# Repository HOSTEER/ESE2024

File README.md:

# ESE2024
    Emilie Butruille
    Louis Liénart
    Théo Césari
    Victor Lesne
------

Activer doxygen dans les propriétés du projet -> général C/C++, tuto doxygen https://www.youtube.com/watch?v=GC9Xy7nLxyw

Pour importer un projet sur cubeIDE, il faut faire "File" -> "Import" -> "General" -> "Project from Folder or Archive" puis sélectionner le directory (exemple "C:\Users\louis\Desktop\ProjetCubeIDE") et ensuite faire "finish".
Après ça, il faut régénérer des fichiers du code, donc cliquer sur "Device configuration tool Code generation"

Avec GitBash, pour retirer un fichier "add" par erreur faire un "git reset nom_du_fichier", un reset seul retirera tout les add fait.

Convention à avoir pour le stockage des sources :
pour stocker les lib créer faire un dossier source "Prod" avec comme sous-fichier "Inc" et "Src"
Ensuite les ajouter dans "Project" -> "Properties" -> "C/C++ General" -> "Paths and Symbols" -> "add" -> entrer "Prod/Inc" et faire ok.

Pour vérifier qu'une branch est ok, cloner un 2nd repo de la branch et la tester pour vérifier l'absence d'erreurs, sinon ça veut dire qu'il manque un truc au commit.

Ensuite il faut résoudre les conflits entre .cproject ( globalement garder le code du main ); .ioc (globalement fusionner les pins ajoutés et faire gaffe au pin, en double) et enfin le main.c ( où il faut fusionner )

conso moyenne 300 mA

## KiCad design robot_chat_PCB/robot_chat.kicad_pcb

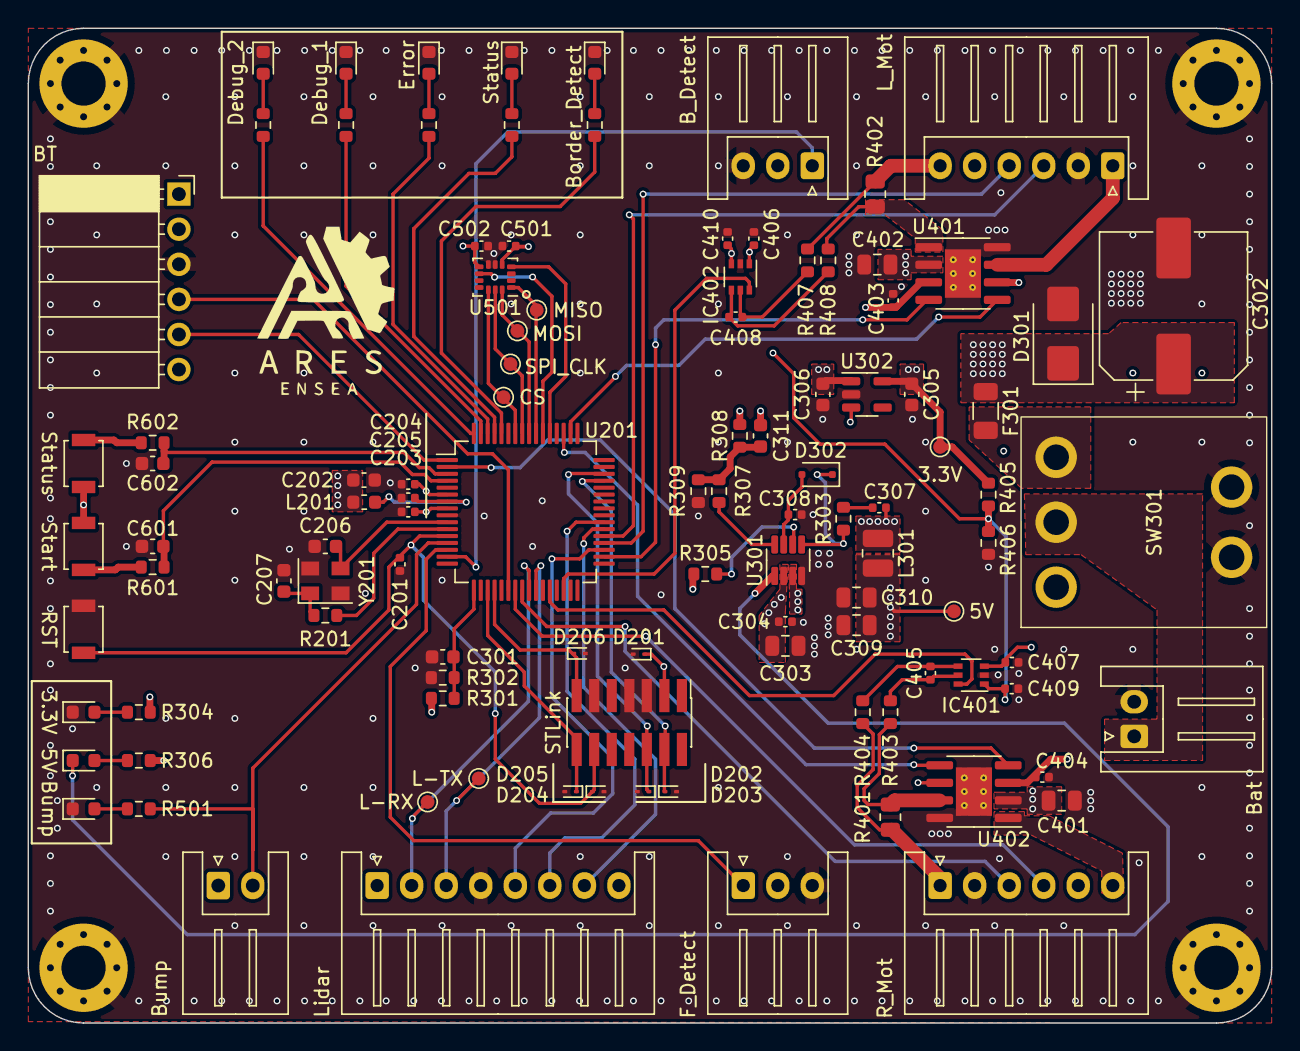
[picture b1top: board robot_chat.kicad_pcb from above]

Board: 4 copper layers, 90.0 x 72.0 mm, 111 parts (0 on the bottom side), 78 nets.

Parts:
+3V301: 3.3V; TestPoint_Pad_D1.0mm
+5V301: 5V; TestPoint_Pad_D1.0mm
C201, C203, C204, C205, C403, C404, C405, C406, C407, C408, C409, C410: 0.1uF; C_0402_1005Metric
C202: 4.7uF; C_0603_1608Metric
C206, C207: 10p; C_0603_1608Metric
C301, C305, C306, C601, C602: 1uF; C_0603_1608Metric
C302: 470uF; CP_Elec_10x10.5
C303, C309, C310, C401, C402: 22uF; C_0805_2012Metric
C304, C307, C308: 0,1uF; C_0402_1005Metric
C311: 15pF; C_0603_1608Metric
C501, C502: 0.1u; C_0402_1005Metric
CS201: CS; TestPoint_Pad_D1.0mm
D201, D202, D203, D204, D205, D206: D_SOD-923
D301: D_SMB
D302: 1N4148; D_SOD-323F
D303: 3.3V; LED_0603_1608Metric
D304: 5V; LED_0603_1608Metric
D501: Bump; LED_0603_1608Metric
D601: Border_Detect; LED_0603_1608Metric
D602: Status; LED_0603_1608Metric
D603: Error; LED_0603_1608Metric
D604: Debug_1; LED_0603_1608Metric
D605: Debug_2; LED_0603_1608Metric
F301: 10A; Fuse_1206_3216Metric
H101, H102, H103, H104: MountingHole_Pad; MountingHole_3.2mm_M3_Pad_Via
IC401, IC402: NCS199A3RSQT2G; SOT-363_SC-70-6
J201: STLink; PinHeader_2x07_P1.27mm_Vertical_SMD
J301: Bat; JST_XH_S2B-XH-A_1x02_P2.50mm_Horizontal
J401: L_Mot; JST_XH_S6B-XH-A_1x06_P2.50mm_Horizontal
J402: R_Mot; JST_XH_S6B-XH-A_1x06_P2.50mm_Horizontal
J501: Bump; JST_XH_S2B-XH-A_1x02_P2.50mm_Horizontal
J502: Lidar; JST_XH_S8B-XH-A_1x08_P2.50mm_Horizontal
J503: B_Detect; JST_XH_S3B-XH-A_1x03_P2.50mm_Horizontal
J504: F_Detect; JST_XH_S3B-XH-A_1x03_P2.50mm_Horizontal
J601: BT; PinSocket_1x06_P2.54mm_Horizontal
L201: 2.2u; L_0603_1608Metric
L301: 4.7uH; L_1008_2520Metric
LIDAR_RX201: L-RX; TestPoint_Pad_D1.0mm
LIDAR_TX201: L-TX; TestPoint_Pad_D1.0mm
R201, R403, R404, R407, R408: 10R; R_0603_1608Metric
R301: 22k; R_0603_1608Metric
R302: 10k; R_0603_1608Metric
R303: 20; R_0603_1608Metric
R304, R306, R501, R601, R602, R603, R604, R605, R606, R607: 1k; R_0603_1608Metric
R305, R405, R406: 100k; R_0603_1608Metric
R307: 16k; R_0603_1608Metric
R308: 40.2k; R_0603_1608Metric
R309: 7.68k; R_0603_1608Metric
R401, R402: 0.015; R_0805_2012Metric
SDI201: MOSI; TestPoint_Pad_D1.0mm
SDO201: MISO; TestPoint_Pad_D1.0mm
SPI_CLK201: SPI_CLK; TestPoint_Pad_D1.0mm
SW201: RST; SW_SPST_B3U-1000P
SW301: SW_SPDT_MSM; Toggle_Switch
SW601: Start; SW_SPST_B3U-1000P
SW602: Status; SW_SPST_B3U-1000P
U201: STM32G070RBTx; LQFP-64_10x10mm_P0.5mm
U301: MP1475DJ-LF-P; TSOT-23-8
U302: MIC5317-3.3xM5; SOT-23-5
U401, U402: ZXBM5210-SP; SOIC-8-1EP_3.9x4.9mm_P1.27mm_EP2.62x3.51mm_ThermalVias
U501: LSM6DSM; LGA-14_3x2.5mm_P0.5mm_LayoutBorder3x4y
Y201: 16MHz; Crystal_SMD_EuroQuartz_MT-4Pin_3.2x2.5mm

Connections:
+3.3V: +3V301.1, C202.1, C203.1, C204.1, C305.1, C403.1, C404.1, C407.1, C410.1, C501.1, C502.1, D201.1 (A1), IC401.3 (VS), IC402.3 (VS), J201.3, J401.5, J402.5, J501.1, J503.2, J504.2, L201.1, R304.2, R405.1, SW601.2, SW602.2, U201.6 (VBAT), U201.8 (VDD), U302.5 (VOUT), U401.3 (VDD), U401.6 (VREF), U402.3 (VDD), U402.6 (VREF), U501.5 (VDDIO), U501.8 (VDD)
+5V: +5V301.1, C306.1, C309.1, C310.1, C311.2, J502.1, J601.2, L301.2, R306.1, R308.2, U302.1 (VIN), U302.3 (EN)
+7.5V: C302.1, C303.1, C304.1, C401.1, C402.1, D301.1 (A1), F301.1, R301.1, R305.1, U301.2 (IN), U401.2 (VM), U402.2 (VM)
/HMI/BT_RX: J601.5, U201.1 (PC11)
/HMI/BT_TX: J601.4, U201.22 (PA5)
/HMI/PB_GAME_START: C601.1, R601.1, U201.4 (PC14)
/HMI/PB_GAME_STATUS: C602.1, R602.1, U201.3 (PC13)
/Motor drivers/ENCODER_L_A: J401.3, U201.37 (PA9/NC)
/Motor drivers/ENCODER_L_B: J401.4, U201.36 (PA8)
/Motor drivers/ENCODER_R_A: J402.3, U201.24 (PA7)
/Motor drivers/ENCODER_R_B: J402.4, U201.23 (PA6)
/Motor drivers/FWD_L: U201.34 (PB14), U401.4 (FWD)
/Motor drivers/FWD_R: U201.2 (PC12), U402.4 (FWD)
/Motor drivers/IN_L+: C408.2, IC402.4 (IN+), R408.2
/Motor drivers/IN_L-: C408.1, IC402.5 (IN-), R407.2
/Motor drivers/IN_R+: C405.2, IC401.4 (IN+), R404.2
/Motor drivers/IN_R-: C405.1, IC401.5 (IN-), R403.2
/Motor drivers/I_READ_L: IC402.6 (OUT), U201.30 (PB10)
/Motor drivers/I_READ_R: IC401.6 (OUT), U201.28 (PB1)
/Motor drivers/MOTOR_L+: J401.1, U401.7 (OUT2)
/Motor drivers/MOTOR_L-: R402.2, R408.1, U401.1 (OUT1)
/Motor drivers/MOTOR_R+: R401.2, R403.1, U402.7 (OUT2)
/Motor drivers/MOTOR_R-: J402.6, U402.1 (OUT1)
/Motor drivers/REV_L: U201.50 (PD0), U401.5 (REV)
/Motor drivers/REV_R: U201.51 (PD1), U402.5 (REV)
/Motor drivers/RSENSE_L-: J401.6, R402.1, R407.1
/Motor drivers/RSENSE_R-: J402.1, R401.1, R404.1
/Motor drivers/VREF: C406.1, C409.1, IC401.1 (REF), IC402.1 (REF), R405.2, R406.1
/Power Supply/BST: D302.1 (K), R303.1, U301.5 (BST)
/Power Supply/EN/SYNC: R305.2, U301.6 (EN/SYNC)
/Power Supply/FB: R307.1, U301.8 (FB)
/Power Supply/PG: D304.1 (K), U301.1 (PG)
/Power Supply/SW: C307.2, L301.1, U301.3 (SW)
/Power Supply/VBAT_READ: C301.2, R301.2, R302.1, U201.17 (PA0)
/Power Supply/VCC: C308.1, D302.2 (A), U301.7 (VCC)
/STM/BACK_BORDER_DETECT: J503.1, U201.15 (PC2)
/STM/BUMPER_SW: J501.2, R501.2, U201.13 (PC0)
/STM/FRONT_BORDER_DETECT: J504.1, U201.14 (PC1)
/STM/IMU_INT1: U201.53 (PD3), U501.4 (INT1)
/STM/IMU_INT2: U201.54 (PD4), U501.9 (INT2)
/STM/IMU_SPI_CLK: SPI_CLK201.1, U201.57 (PB3), U501.13 (SCL)
/STM/IMU_SPI_CS: CS201.1, U201.58 (PB4), U501.12 (CS)
/STM/IMU_SPI_SDI: SDI201.1, U201.56 (PD6), U501.14 (SDA)
/STM/IMU_SPI_SDO: SDO201.1, U201.55 (PD5), U501.1 (SDO/SA0)
/STM/LIDAR_EN: J502.7, U201.38 (PC6)
/STM/LIDAR_RANGING_EN: J502.6, U201.39 (PC7)
/STM/LIDAR_RX: J502.2, LIDAR_RX201.1, U201.25 (PC4)
/STM/LIDAR_SPEED: J502.5, U201.35 (PB15)
/STM/LIDAR_TX: J502.3, LIDAR_TX201.1, U201.26 (PC5)
/STM/QUARTZ_0: C206.2, U201.10 (PF0), Y201.3
/STM/QUARTZ_1: R201.2, U201.11 (PF1)
/STM/STLINK_RX: D206.1 (A1), J201.13, U201.20 (PA3)
/STM/STLINK_TX: D205.1 (A1), J201.14, U201.19 (PA2)
/STM/SWCLK: D203.1 (A1), J201.6, U201.46 (PA14)
/STM/SWDIO: D202.1 (A1), J201.4, U201.45 (PA13)
/STM/VREF+: C205.2, L201.2, U201.7 (VREF+)
/STM/~RST: C201.2, D204.1 (A1), J201.12, SW201.2, U201.12 (NRST)
GND: C201.1, C202.2, C203.2, C204.2, C205.1, C206.1, C207.1, C301.1, C302.2, C303.2, C304.2, C305.2, C306.2, C308.2, C309.2, C310.2, C401.2, C402.2, C403.2, C404.2, C406.2, C407.2, C409.2, C410.2, C501.2, C502.2, C601.2, C602.2, D201.2 (A2), D202.2 (A2), D203.2 (A2), D204.2 (A2), D205.2 (A2), D206.2 (A2), D301.2 (A2), D303.1 (K), D501.1 (K), D601.1 (K), D602.1 (K), D603.1 (K), D604.1 (K), D605.1 (K), H101.1, H102.1, H103.1, H104.1, IC401.2 (GND), IC402.2 (GND), J201.5, J201.7, J201.11, J301.2, J401.2, J402.2, J502.4, J503.3, J504.3, J601.3, R302.2, R309.2, R406.2, SW201.1, SW301.4, SW301.5, U201.9 (VSS), U301.4 (GND), U302.2 (GND), U401.8 (GND), U401.9 (GND), U402.8 (GND), U402.9 (GND), U501.6 (GND), U501.7 (GND), Y201.2, Y201.4
unnamed: C207.2, R201.1, Y201.1
unnamed: C307.1, R303.2
unnamed: C311.1, R307.2, R308.1, R309.1
unnamed: D303.2 (A), R304.1
unnamed: D304.2 (A), R306.2
unnamed: D501.2 (A), R501.1
unnamed: D601.2 (A), R603.2
unnamed: D602.2 (A), R604.2
unnamed: D603.2 (A), R605.2
unnamed: D604.2 (A), R606.2
unnamed: D605.2 (A), R607.2
unnamed: F301.2, SW301.1
unnamed: J301.1, SW301.2
unnamed: R601.2, SW601.1
unnamed: R602.2, SW602.1
USER_LED_0: R603.1, U201.60 (PB6)
USER_LED_1: R604.1, U201.61 (PB7)
USER_LED_2: R605.1, U201.62 (PB8)
USER_LED_3: R606.1, U201.63 (PB9)
USER_LED_4: R607.1, U201.64 (PC10)

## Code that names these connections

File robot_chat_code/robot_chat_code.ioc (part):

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Mcu.Name=STM32G070RBTx
Mcu.Package=LQFP64
Mcu.UserName=STM32G070RBTx
PA0.GPIOParameters=GPIO_Label
PA0.GPIO_Label=BAT_ADC
PA0.Mode=IN0
PA0.Signal=ADC1_IN0
PA13.Mode=Serial_Wire
PA13.Signal=SYS_SWDIO
PA14-BOOT0.Mode=Serial_Wire
PA14-BOOT0.Signal=SYS_SWCLK
PA2.GPIOParameters=GPIO_Label
PA2.GPIO_Label=ST_LINK_TX
PA2.Mode=Asynchronous
PA2.Signal=USART2_TX
PA3.GPIOParameters=GPIO_Label
PA3.GPIO_Label=ST_LINK_RX
PA3.Mode=Asynchronous
PA3.Signal=USART2_RX
PA5.GPIOParameters=GPIO_Label
PA5.GPIO_Label=BT_TX
PA5.Mode=Asynchronous
PA5.Signal=USART3_TX
PA6.GPIOParameters=GPIO_Label
PA6.GPIO_Label=R_ENCODE_B
PA6.Signal=S_TIM3_CH1
PA7.GPIOParameters=GPIO_Label
PA7.GPIO_Label=R_ENCODE_A
PA7.Signal=S_TIM3_CH2
PA8.GPIOParameters=GPIO_Label
PA8.GPIO_Label=L_ENCODE_B
PA8.Signal=S_TIM1_CH1
PA9.GPIOParameters=GPIO_Label
PA9.GPIO_Label=L_ENCODE_A
PA9.Signal=S_TIM1_CH2
PB1.GPIOParameters=GPIO_Label
PB1.GPIO_Label=I_READ_R
PB1.Mode=IN9
PB1.Signal=ADC1_IN9
PB10.GPIOParameters=GPIO_Label
PB10.GPIO_Label=I_READ_L
PB10.Mode=IN11
PB10.Signal=ADC1_IN11
PB14.GPIOParameters=GPIO_Label
PB14.GPIO_Label=L_FORWARD
PB14.Signal=S_TIM15_CH1
PB15.GPIOParameters=GPIO_Label
PB15.GPIO_Label=LIDAR_SPEED
PB15.Signal=S_TIM15_CH2
PB3.GPIOParameters=GPIO_Label
PB3.GPIO_Label=IMU_SPI_CLK
PB3.Mode=Full_Duplex_Master
PB3.Signal=SPI1_SCK
PB4.GPIOParameters=PinState,GPIO_Label
PB4.GPIO_Label=IMU_SPI_CS
PB4.PinState=GPIO_PIN_SET
PB4.Signal=GPIO_Output
PB6.GPIOParameters=GPIO_Label
PB6.GPIO_Label=USER_LED0
PB6.Signal=GPIO_Output
PB7.GPIOParameters=GPIO_Label
PB7.GPIO_Label=USER_LED1
PB7.Signal=GPIO_Output
PB8.GPIOParameters=GPIO_Label
PB8.GPIO_Label=USER_LED2
PB8.Signal=GPIO_Output
PB9.GPIOParameters=GPIO_Label
PB9.GPIO_Label=USER_LED3
PB9.Signal=GPIO_Output
PC0.GPIOParameters=GPIO_Label
PC0.GPIO_Label=BUMP_EXTI
PC0.Signal=GPIO_Input
PC1.GPIOParameters=GPIO_PuPd,GPIO_Label,GPIO_ModeDefaultEXTI
PC1.GPIO_Label=FBD_EXTI1
PC1.GPIO_ModeDefaultEXTI=GPIO_MODE_IT_RISING_FALLING
PC1.GPIO_PuPd=GPIO_PULLDOWN
PC1.Signal=GPXTI1
PC10.GPIOParameters=GPIO_Label
PC10.GPIO_Label=USER_LED4
PC10.Signal=GPIO_Output
PC11.GPIOParameters=GPIO_Label
PC11.GPIO_Label=BT_RX
PC11.Mode=Asynchronous
PC11.Signal=USART3_RX
PC12.GPIOParameters=GPIO_Label
PC12.GPIO_Label=R_FORWARD
PC12.Signal=S_TIM14_CH1
PC13.GPIOParameters=GPIO_PuPd,GPIO_Label,GPIO_ModeDefaultEXTI
PC13.GPIO_Label=BTN_GAME_STATUS
PC13.GPIO_ModeDefaultEXTI=GPIO_MODE_IT_RISING
PC13.GPIO_PuPd=GPIO_PULLDOWN
PC13.Signal=GPXTI13
PC14-OSC32_IN\ (PC14).GPIOParameters=GPIO_PuPd,GPIO_Label
PC14-OSC32_IN\ (PC14).GPIO_Label=BTN_GAME_START
PC14-OSC32_IN\ (PC14).GPIO_PuPd=GPIO_PULLDOWN
PC14-OSC32_IN\ (PC14).Signal=GPXTI14
PC2.GPIOParameters=GPIO_PuPd,GPIO_Label,GPIO_ModeDefaultEXTI
PC2.GPIO_Label=BBD_EXTI2
PC2.GPIO_ModeDefaultEXTI=GPIO_MODE_IT_RISING_FALLING
PC2.GPIO_PuPd=GPIO_PULLDOWN
PC2.Signal=GPXTI2
PC4.GPIOParameters=GPIO_Label
PC4.GPIO_Label=LIDAR_TX
PC4.Mode=Asynchronous
PC4.Signal=USART1_TX
PC5.GPIOParameters=GPIO_Label
PC5.GPIO_Label=LIDAR_RX
PC5.Mode=Asynchronous
PC5.Signal=USART1_RX
PC6.GPIOParameters=GPIO_Label
PC6.GPIO_Label=LIDAR_EN
PC6.Signal=GPIO_Output
PC7.GPIOParameters=GPIO_Label
PC7.GPIO_Label=LIDAR_RANGING_EN
PC7.Signal=GPIO_Output
PD0.GPIOParameters=GPIO_Label
PD0.GPIO_Label=L_REVERSE
PD0.Signal=S_TIM16_CH1
PD1.GPIOParameters=GPIO_Label
PD1.GPIO_Label=R_REVERSE
PD1.Signal=S_TIM17_CH1
PD3.GPIOParameters=GPIO_Label
PD3.GPIO_Label=IMU_INT1
PD3.Signal=GPXTI3
PD4.GPIOParameters=GPIO_Label
PD4.GPIO_Label=IMU_INT2
PD4.Signal=GPXTI4
PD5.GPIOParameters=GPIO_Label
PD5.GPIO_Label=IMU_SPI_SDO
PD5.Mode=Full_Duplex_Master
PD5.Signal=SPI1_MISO
PD6.GPIOParameters=GPIO_Label
PD6.GPIO_Label=IMU_SPI_SDI
PD6.Mode=Full_Duplex_Master
PD6.Signal=SPI1_MOSI
PF0-OSC_IN\ (PF0).Mode=HSE-External-Oscillator
PF0-OSC_IN\ (PF0).Signal=RCC_OSC_IN
PF1-OSC_OUT\ (PF1).Mode=HSE-External-Oscillator
PF1-OSC_OUT\ (PF1).Signal=RCC_OSC_OUT
RCC.HSE_VALUE=16000000
RCC.SYSCLKFreq_VALUE=64000000
RCC.SYSCLKSource=RCC_SYSCLKSOURCE_PLLCLK
board=custom

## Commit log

2023-09-18 schema fonctionnement
2023-09-18 BOM v1
2023-09-18 test
2023-09-18 ready2
2023-09-18 ready5
2023-09-18 ready10
2023-09-19 Schema fonctionnel v1
2023-09-19 Schema fonctionnel v2
2023-09-19 image readme
2023-09-19 image readme v2
2023-09-19 AddingPins
2023-09-19 image readme v3
2023-09-19 image readme v4 et datasheets
2023-09-19 shah
2023-09-19 PIN CubeIDE et PCB
2023-09-19 Project re-upload
2023-09-20 ajout BOM v2
2023-09-20 premier modif
2023-09-20 pcb alim et connecteurs
2023-09-21 addPin
2023-09-21 Ajout lecture courant et enable lidar sur ioc
2023-09-21 Modif PCB
2023-09-21 lidar_dev
2023-09-22 Ajout IMU
2023-09-22 Ajout IMU pcb
2023-09-25 addingLibLIdar
2023-09-25 Labels non reliés pour BOM
2023-09-25 PCB revu
2023-09-25 Ajout game start
2023-09-25 ajout BOM
2023-09-25 progessLib
2023-09-25 PCB final avec BOM
2023-09-27 lib change
2023-09-28 upgrade_lib_fonctionnel
2023-09-28 Placement composants
2023-09-28 upgrade_lecture_first_frame
2023-09-29 minimodif
2023-10-02 Mise à jour placement
2023-10-02 changed Rsense position
2023-10-02 lecture_angle
2023-10-03 parser_ok
2023-10-03 Mise à jour led bumper
2023-10-04 function_simplification
2023-10-04 gettingsmpl
2023-10-05 Lidar data extracted
2023-10-05 Routage
2023-10-06 Lidar data computing
2023-10-06 improve lib
2023-10-09 Nom des fonctions & variables changé de ylidar à ydlidar
2023-10-09 Routage final v1
2023-10-09 changed pinout
2023-10-09 routage final v1.1
2023-10-09 correct lidar lib and adding lidar visualizer
2023-10-16 Routage final v1.2
2023-10-16 adding encoder test project
2023-10-26 fixed DRC, added html bom
2023-11-01 nom plus simple dans le main de variable de structure et re-ajout des distances sur 360 deg avec un choix ifdef
2023-11-01 simplifying variable name in function by lidar instead of ydlidar_x4
2023-11-13 test MCU avec freetos et test user led ok
2023-11-13 ajout du BT pour le print
2023-11-13 Start of IMU driver
2023-11-13 IMU dev init
2023-11-13 ajout lidar en cours, ajouter l'etape de calcule
2023-11-22 reception et envoie des donnees lidar utilisable
2023-11-23 SPI communicant
2023-11-23 lidar ok sans DMA pour linstant
2023-11-29 improving lidar dev demo stability
2023-11-29 lidar ok sur PCB robot chat
2023-12-01 lidar ok pour PCB chat
2023-12-01 Fonction de lecture et d'écriture d'un registre
2023-12-01 Rebase de ajout moteur
2023-12-02 Boucle de lecture de rotation et tache de printf
2023-12-02 added motor driver
2023-12-02 added motor speed and current sensing
2023-12-03 fixed current sensing, added battery voltage sensing
2023-12-04 added fixed point math and speed PID V1
2023-12-05 implemented saturation, and feedforward
2023-12-07 reduced latency and disable angle shifting in processing
2023-12-07 testing max port delay
2023-12-08 correction angle
2023-12-08 lidar ok avec moteur
2023-12-08 ajout mot gauche
2023-12-10 added odometry, changed PID frequency and parameters
2023-12-10 fixed OCD triggering and deadlock issue
2023-12-10 added angular control, fixed odometry
2023-12-11 Fin 1ere phase programmation IMU
2023-12-11 IMU merge ok
2023-12-11 Debut dev capt chute
2023-12-11 Rising edge cb fonctionnel, Falling edge ne se declanchant pas
2023-12-12 Adding new ST project
2023-12-12 test .h
2023-12-12 new project ok
2023-12-12 new project ok to test
2023-12-12 Vector mode CORDIC
2023-12-13 IOC modifie et ajout var de strategie
2023-12-13 reupload capt_chute
2023-12-13 Suppression des .metadata du repo
2023-12-13 modif pour lidar
2023-12-13 lidar ok for old project
2023-12-13 Debut fonction de strategie et champ vectoriel
2023-12-13 follow trajectory
2023-12-13 lidar almost working
2023-12-14 Champ vectoriel implemente
2023-12-14 Correction conflits init et prototypes de fonctions
2023-12-14 Champ vectoriel avec un offset unique pour tous les cotes (necessaire pour les courbes de suivi circulaires)
2023-12-14 Utilisation des fonctions * et / en virgule fixe
2023-12-18 LSN issue fix
2023-12-18 Fonctions de champ de vect implementes
2023-12-18 Suivi de courbe lineaire implemente, la correction d'ecartement fonctionne
2023-12-18 Cas de chute et collision implementes
2023-12-18 Ajout code au projet robot_chat_soft
2023-12-18 ading tracking
2023-12-18 adding bt
2023-12-18 processing
2023-12-19 cordic bugfix
2023-12-19 Branche main-compatible
2023-12-19 Zone circulaire implementee
2023-12-19 lidar tracking
2023-12-19 Commande de suivi de ligne a tester
2023-12-19 move to new project, lidar tracking bugfix
2023-12-20 code a tester
2023-12-20 Printf par interruption fonctionnel
2023-12-20 Probleme d'overflow de l'odom regle, strat a tester sur le robot
2023-12-20 patched odometry overflow
2023-12-21 removed ydlidar_x4_init from main.c
2023-12-21 fixed cos/sin
2023-12-21 Vecteur de consigne fiable (sans overflow) et printf en DMA
2023-12-21 segmentation envoie serie et pb angle 350 - 12
2023-12-21 mask
2023-12-21 trajectory bugfix
2023-12-21 patched modulo_2pi, improved angle controller
2023-12-21 simplification code concernant les angles start et end
2023-12-22 before merge from main
2023-12-22 fction init du lidar ok
2023-12-22 taget dist from center
2023-12-22 chat soft ok
2023-12-22 test compilation
2023-12-22 target shape angles
2023-12-22 Prise en compte des bumpers et capteurs de chute dans la stratégie
2024-01-08 test target struct
2024-01-08 target choice functional
2024-01-08 Code strategie v1
2024-01-08 adding lib comment
2024-01-08 functional target detect
2024-01-11 Robot fonctionnel v2
2024-01-11 Robot fonctionnel v3
2024-01-12 adding target search in mask
2024-01-12 Robot fonctionnel v4
2024-01-12 lidar okk
